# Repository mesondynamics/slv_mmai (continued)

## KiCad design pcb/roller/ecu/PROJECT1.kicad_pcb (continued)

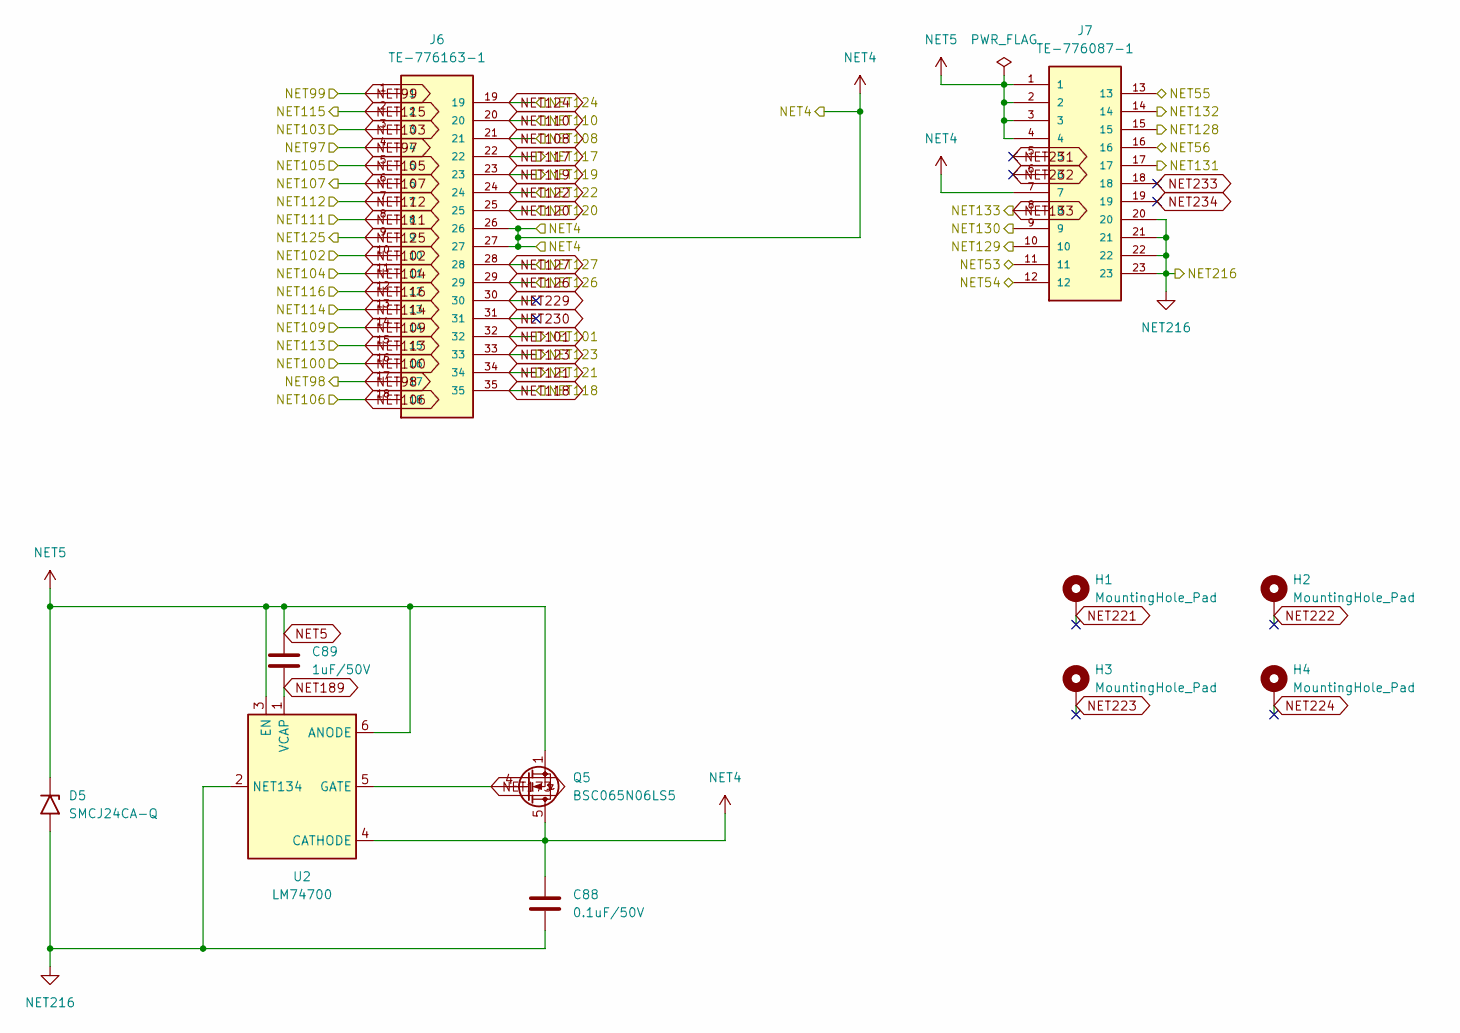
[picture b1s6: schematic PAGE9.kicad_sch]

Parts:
C88: 0.1uF/50V; C_0603_1608Metric
C89: 1uF/50V; C_0603_1608Metric
D5: SMCJ24CA-Q; D_SMC
H1, H2, H3, H4: MountingHole_Pad; MountingHole_3.2mm_M3_ISO7380_Pad
J6: TE-776163-1; TE_776163-1
J7: TE-776087-1; TE_776087-1; PARTREV E11
Q5: BSC065N06LS5; TDSON-8-1
U2: LM74700; SOT-23-6

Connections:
NET4: C88.1, J6.26, J6.27, J7.7, Q5.5 (D), U2.4 (CATHODE); also elsewhere on the board
NET5: C89.1, D5.1 (A1), J7.1, J7.2, J7.3, J7.4, Q5.1 (S), Q5.2 (S), Q5.3 (S), U2.3 (EN), U2.6 (ANODE); also elsewhere on the board
NET53: J7.11; also elsewhere on the board
NET54: J7.12; also elsewhere on the board
NET55: J7.13; also elsewhere on the board
NET56: J7.16; also elsewhere on the board
NET97: J6.4; also elsewhere on the board
NET98: J6.17; also elsewhere on the board
NET99: J6.1; also elsewhere on the board
NET100: J6.16; also elsewhere on the board
NET101: J6.32; also elsewhere on the board
NET102: J6.10; also elsewhere on the board
NET103: J6.3; also elsewhere on the board
NET104: J6.11; also elsewhere on the board
NET105: J6.5; also elsewhere on the board
NET106: J6.18; also elsewhere on the board
NET107: J6.6; also elsewhere on the board
NET108: J6.21; also elsewhere on the board
NET109: J6.14; also elsewhere on the board
NET110: J6.20; also elsewhere on the board
NET111: J6.8; also elsewhere on the board
NET112: J6.7; also elsewhere on the board
NET113: J6.15; also elsewhere on the board
NET114: J6.13; also elsewhere on the board
NET115: J6.2; also elsewhere on the board
NET116: J6.12; also elsewhere on the board
NET117: J6.22; also elsewhere on the board
NET118: J6.35; also elsewhere on the board
NET119: J6.23; also elsewhere on the board
NET120: J6.25; also elsewhere on the board
NET121: J6.34; also elsewhere on the board
NET122: J6.24; also elsewhere on the board
NET123: J6.33; also elsewhere on the board
NET124: J6.19; also elsewhere on the board
NET125: J6.9; also elsewhere on the board
NET126: J6.29; also elsewhere on the board
NET127: J6.28; also elsewhere on the board
NET128: J7.15; also elsewhere on the board
NET129: J7.10; also elsewhere on the board
NET130: J7.9; also elsewhere on the board
NET131: J7.17; also elsewhere on the board
NET132: J7.14; also elsewhere on the board
NET133: J7.8; also elsewhere on the board
NET173: Q5.4 (G), U2.5 (GATE)
NET189: C89.2, U2.1 (VCAP)
NET216: C88.2, D5.2 (A2), J7.20, J7.21, J7.22, J7.23, U2.2 (GND); also elsewhere on the board
NET221: H1.1 (1_1)
NET222: H2.1 (1_1)
NET223: H3.1 (1_1)
NET224: H4.1 (1_1)
NET229: J6.30
NET230: J6.31
NET231: J7.5
NET232: J7.6
NET233: J7.18
NET234: J7.19

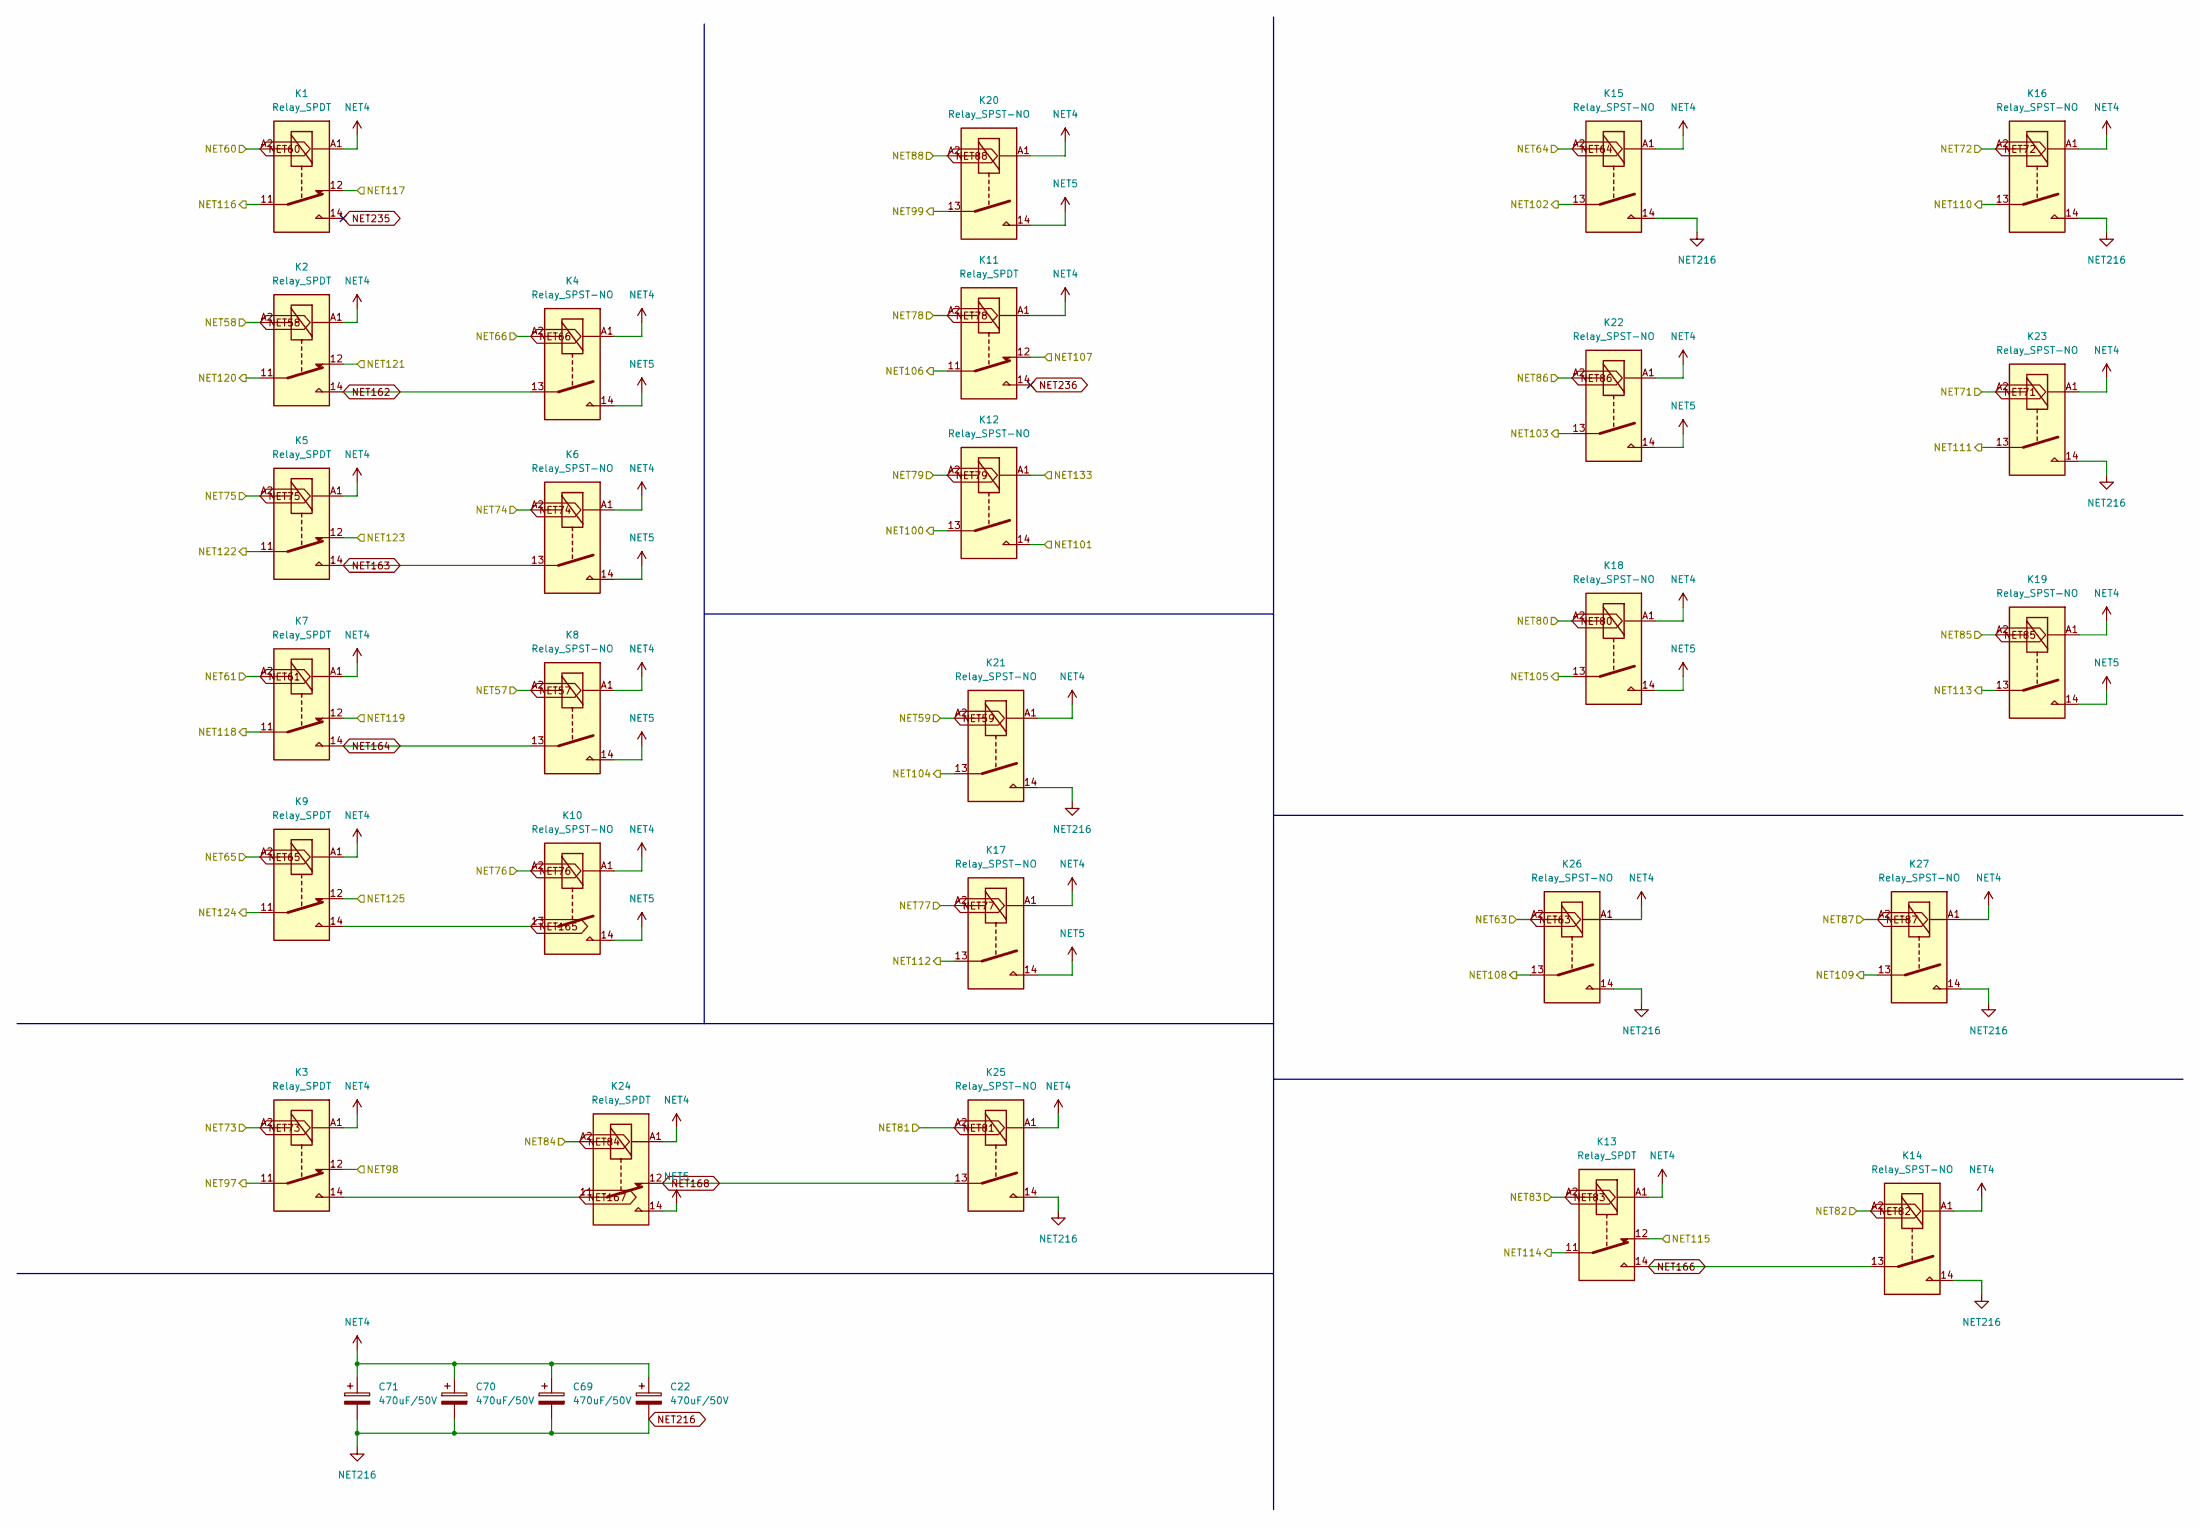
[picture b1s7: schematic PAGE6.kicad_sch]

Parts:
C22, C69, C70, C71: 470uF/50V; CP_Elec_5x5.4
K1, K2, K3, K5, K7, K9, K11, K13, K24: Relay_SPDT; Relay_SPDT_Hongfa_HFV6_1FormC
K4, K6, K8, K10, K12, K14, K15, K16, K17, K18, K19, K20, K21, K22, K23, K25, K26, K27: Relay_SPST-NO; Relay_SPST-NO_Hongfa_HFV6_1FormA

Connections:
NET4: C22.1, C69.1, C70.1, C71.1, K1.A1, K2.A1, K3.A1, K4.A1, K5.A1, K6.A1, K7.A1, K8.A1, K9.A1, K10.A1, K11.A1, K13.A1, K14.A1, K15.A1, K16.A1, K17.A1, K18.A1, K19.A1, K20.A1, K21.A1, K22.A1, K23.A1, K24.A1, K25.A1, K26.A1, K27.A1; also elsewhere on the board
NET5: K4.14, K6.14, K8.14, K10.14, K17.14, K18.14, K19.14, K20.14, K22.14, K24.14; also elsewhere on the board
NET57: K8.A2; also elsewhere on the board
NET58: K2.A2; also elsewhere on the board
NET59: K21.A2; also elsewhere on the board
NET60: K1.A2; also elsewhere on the board
NET61: K7.A2; also elsewhere on the board
NET63: K26.A2; also elsewhere on the board
NET64: K15.A2; also elsewhere on the board
NET65: K9.A2; also elsewhere on the board
NET66: K4.A2; also elsewhere on the board
NET71: K23.A2; also elsewhere on the board
NET72: K16.A2; also elsewhere on the board
NET73: K3.A2; also elsewhere on the board
NET74: K6.A2; also elsewhere on the board
NET75: K5.A2; also elsewhere on the board
NET76: K10.A2; also elsewhere on the board
NET77: K17.A2; also elsewhere on the board
NET78: K11.A2; also elsewhere on the board
NET79: K12.A2; also elsewhere on the board
NET80: K18.A2; also elsewhere on the board
NET81: K25.A2; also elsewhere on the board
NET82: K14.A2; also elsewhere on the board
NET83: K13.A2; also elsewhere on the board
NET84: K24.A2; also elsewhere on the board
NET85: K19.A2; also elsewhere on the board
NET86: K22.A2; also elsewhere on the board
NET87: K27.A2; also elsewhere on the board
NET88: K20.A2; also elsewhere on the board
NET97: K3.11; also elsewhere on the board
NET98: K3.12; also elsewhere on the board
NET99: K20.13; also elsewhere on the board
NET100: K12.13; also elsewhere on the board
NET101: K12.14; also elsewhere on the board
NET102: K15.13; also elsewhere on the board
NET103: K22.13; also elsewhere on the board
NET104: K21.13; also elsewhere on the board
NET105: K18.13; also elsewhere on the board
NET106: K11.11; also elsewhere on the board
NET107: K11.12; also elsewhere on the board
NET108: K26.13; also elsewhere on the board
NET109: K27.13; also elsewhere on the board
NET110: K16.13; also elsewhere on the board
NET111: K23.13; also elsewhere on the board
NET112: K17.13; also elsewhere on the board
NET113: K19.13; also elsewhere on the board
NET114: K13.11; also elsewhere on the board
NET115: K13.12; also elsewhere on the board
NET116: K1.11; also elsewhere on the board
NET117: K1.12; also elsewhere on the board
NET118: K7.11; also elsewhere on the board
NET119: K7.12; also elsewhere on the board
NET120: K2.11; also elsewhere on the board
NET121: K2.12; also elsewhere on the board
NET122: K5.11; also elsewhere on the board
NET123: K5.12; also elsewhere on the board
NET124: K9.11; also elsewhere on the board
NET125: K9.12; also elsewhere on the board
NET133: K12.A1; also elsewhere on the board
NET162: K2.14, K4.13
NET163: K5.14, K6.13
NET164: K7.14, K8.13
NET165: K9.14, K10.13
NET166: K13.14, K14.13
NET167: K3.14, K24.11
NET168: K24.12, K25.13
NET216: C22.2, C69.2, C70.2, C71.2, K14.14, K15.14, K16.14, K21.14, K23.14, K25.14, K26.14, K27.14; also elsewhere on the board
NET235: K1.14
NET236: K11.14

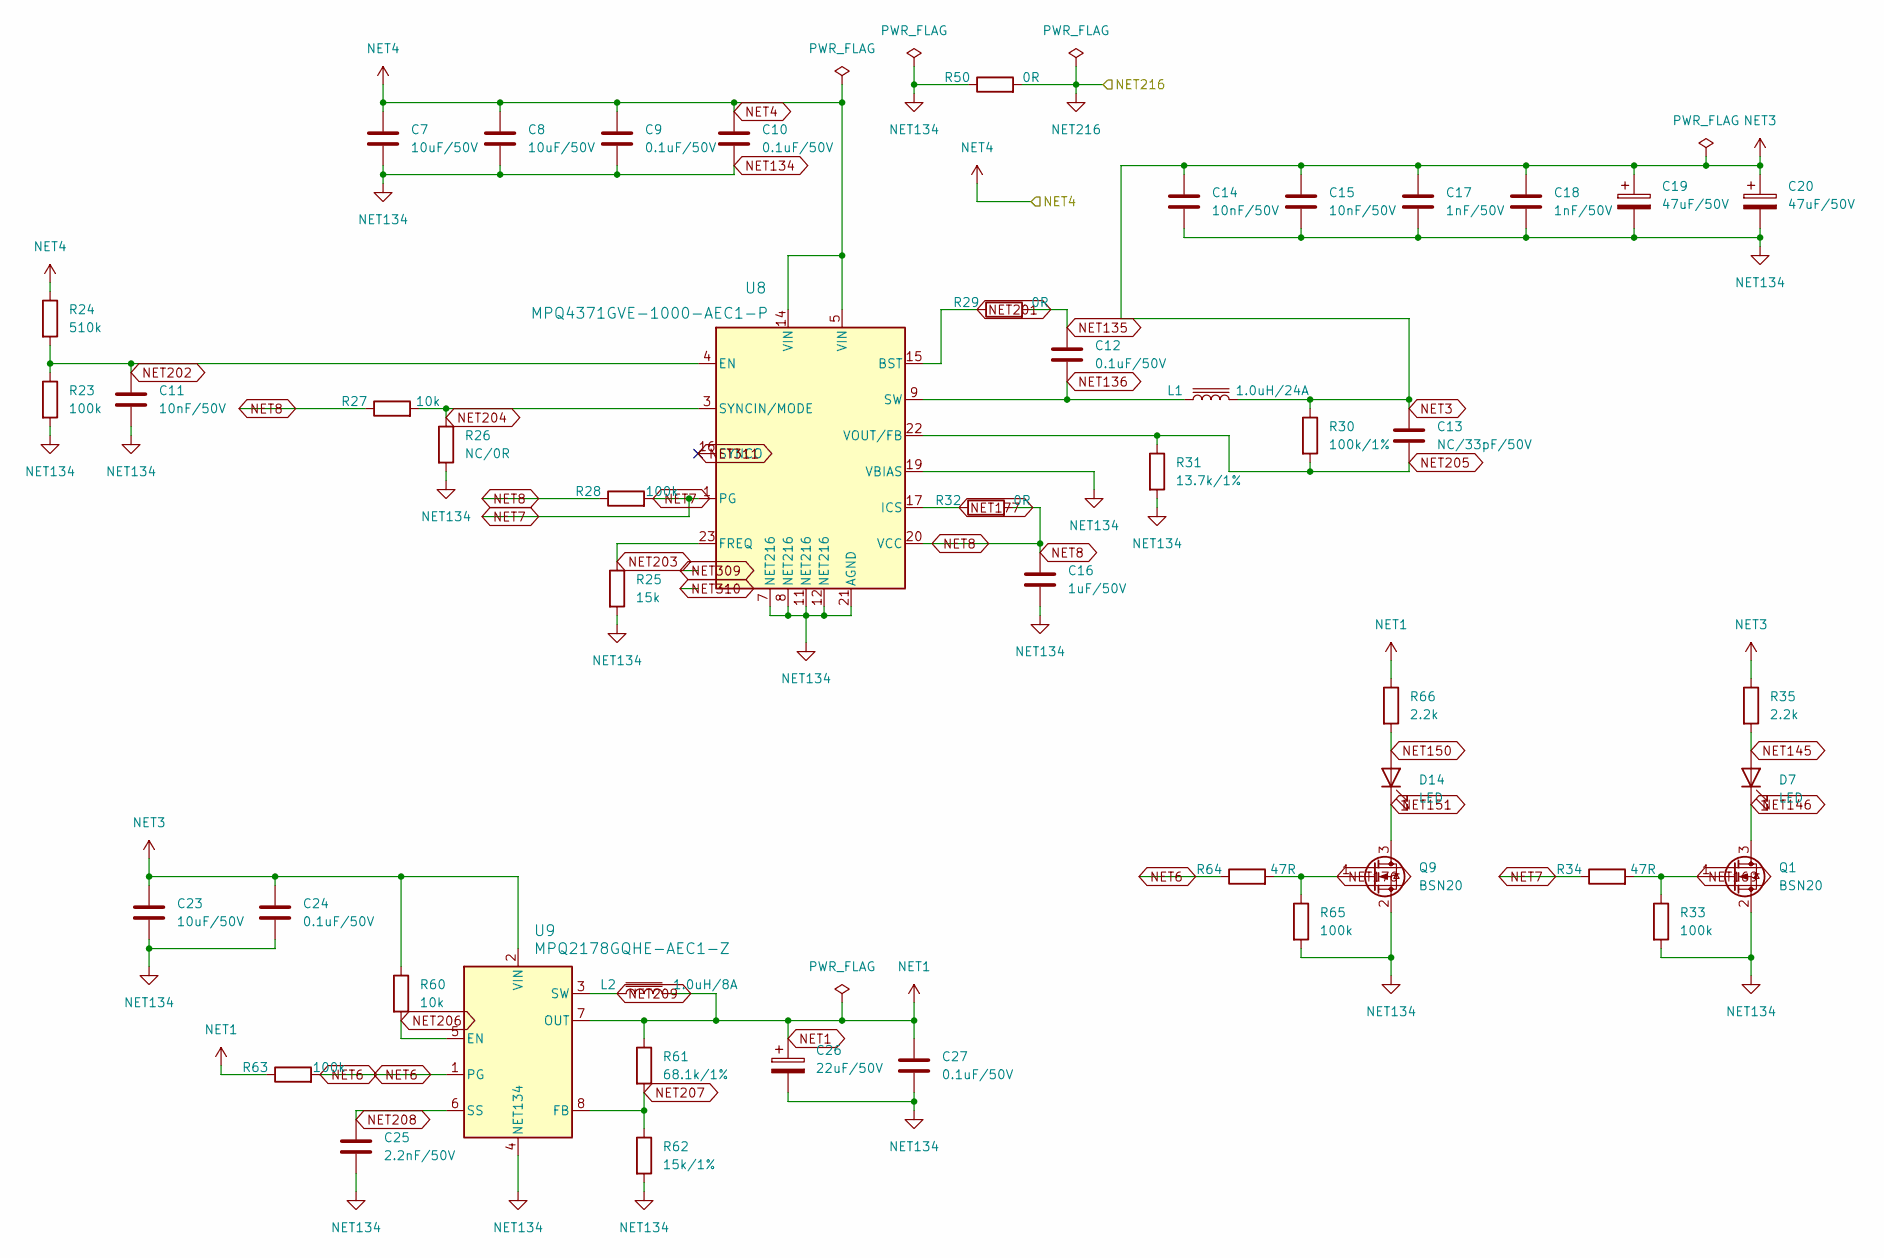
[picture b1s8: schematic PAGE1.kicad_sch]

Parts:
C7, C8, C23: 10uF/50V; C_0603_1608Metric
C9, C10, C12, C24, C27: 0.1uF/50V; C_0603_1608Metric
C11, C14, C15: 10nF/50V; C_0603_1608Metric
C13: NC/33pF/50V; C_0603_1608Metric
C16: 1uF/50V; C_0603_1608Metric
C17, C18: 1nF/50V; C_0603_1608Metric
C19, C20: 47uF/50V; CP_Elec_5x5.4
C25: 2.2nF/50V; C_0603_1608Metric
C26: 22uF/50V; CP_Elec_5x5.4
D7, D14: LED; LED_0603_1608Metric
L1: 1.0uH/24A; L_APV_APH1040
L2: 1.0uH/8A; L_APV_APH0630
Q1, Q9: BSN20; SOT-23
R23, R28, R33, R63, R65: 100k; R_0603_1608Metric
R24: 510k; R_0603_1608Metric
R25: 15k; R_0603_1608Metric
R26: NC/0R; R_0603_1608Metric
R27, R60: 10k; R_0603_1608Metric
R29, R32, R50: 0R; R_0603_1608Metric
R30: 100k/1%; R_0603_1608Metric
R31: 13.7k/1%; R_0603_1608Metric
R34, R64: 47R; R_0603_1608Metric
R35, R66: 2.2k; R_0603_1608Metric
R61: 68.1k/1%; R_0603_1608Metric
R62: 15k/1%; R_0603_1608Metric
U8: MPQ4371GVE-1000-AEC1-P; QFN-234MMX5MM_MPQ4371_MNP
U9: MPQ2178GQHE-AEC1-Z; QFN-8_MPQ2178GQHE

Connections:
NET1: C26.1, C27.1, L2.2, R61.1, R63.1, R66.1, U9.7 (OUT); also elsewhere on the board
NET3: C13.1, C14.1, C15.1, C17.1, C18.1, C19.1, C20.1, C23.1, C24.1, L1.2, R30.1, R35.1, R60.1, U9.2 (VIN); also elsewhere on the board
NET4: C7.1, C8.1, C9.1, C10.1, R24.1, U8.5 (VIN), U8.14 (VIN); also elsewhere on the board
NET6: R63.2, R64.1, U9.1 (PG)
NET7: R28.2, R34.1, U8.1 (PG), U8.2 (PG)
NET8: C16.1, R27.1, R28.1, R32.2, U8.20 (VCC)
NET134: C7.2, C8.2, C9.2, C10.2, C11.2, C14.2, C15.2, C16.2, C17.2, C18.2, C19.2, C20.2, C23.2, C24.2, C25.2, C26.2, C27.2, Q1.2 (S), Q9.2 (S), R23.2, R25.2, R26.2, R31.2, R33.2, R50.1, R62.2, R65.2, U8.7 (PGND), U8.8 (PGND), U8.11 (PGND), U8.12 (PGND), U8.19 (VBIAS), U8.21 (AGND), U9.4 (GND); also elsewhere on the board
NET135: C12.1, R29.2
NET136: C12.2, L1.1, U8.9 (SW), U8.10 (SW)
NET145: D7.2 (A), R35.2
NET146: D7.1 (K), Q1.3 (D)
NET150: D14.2 (A), R66.2
NET151: D14.1 (K), Q9.3 (D)
NET169: Q1.1 (G), R33.1, R34.2
NET176: Q9.1 (G), R64.2, R65.1
NET177: R32.1, U8.17 (ICS), U8.18 (ICS)
NET201: R29.1, U8.15 (BST)
NET202: C11.1, R23.1, R24.2, U8.4 (EN)
NET203: R25.1, U8.23 (FREQ)
NET204: R26.1, R27.2, U8.3 (SYNCIN/MODE)
NET205: C13.2, R30.2, R31.1, U8.22 (VOUT/FB)
NET206: R60.2, U9.5 (EN)
NET207: R61.2, R62.1, U9.8 (FB)
NET208: C25.1, U9.6 (SS)
NET209: L2.1, U9.3 (SW)
NET216: R50.2; also elsewhere on the board
NET309: U8.6 (NC)
NET310: U8.13 (NC)
NET311: U8.16 (SYNCO)

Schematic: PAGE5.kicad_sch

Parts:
C5, C21, C66, C67, C68: 100nF; C_0603_1608Metric
Q6: 2N7002KQ-7; SOT-23
R71: 1.5k; R_0603_1608Metric
R72, R73, R74, R75, R76: 10k; R_0603_1608Metric
R77: 330R; R_0603_1608Metric
R78: 100k; R_0603_1608Metric
U300: SN74AHCT541QPWRQ1; TSSOP-20_4.4x6.5mm_P0.65mm
U301, U302, U303, U304: TPIC6A595DWR; SOIC-24W_7.5x15.4mm_P1.27mm

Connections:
NET3: C5.1, C21.1, C66.1, C67.1, C68.1, R71.1, R72.1, U300.20 (VCC), U301.21 (VCC), U302.21 (VCC), U303.21 (VCC), U304.21 (VCC); also elsewhere on the board
NET33: U300.5 (A3); also elsewhere on the board
NET34: R77.1; also elsewhere on the board
NET35: U300.6 (A4); also elsewhere on the board
NET36: U300.4 (A2); also elsewhere on the board
NET37: U300.2 (A0); also elsewhere on the board
NET38: U300.3 (A1); also elsewhere on the board
NET57: U301.23 (DRAIN0); also elsewhere on the board
NET58: U301.24 (DRAIN1); also elsewhere on the board
NET59: U301.1 (DRAIN2); also elsewhere on the board
NET60: U301.2 (DRAIN3); also elsewhere on the board
NET61: U301.11 (DRAIN4); also elsewhere on the board
NET62: U301.12 (DRAIN5)
NET63: U301.13 (DRAIN6); also elsewhere on the board
NET64: U301.14 (DRAIN7); also elsewhere on the board
NET65: U302.23 (DRAIN0); also elsewhere on the board
NET66: U302.24 (DRAIN1); also elsewhere on the board
NET67: U302.1 (DRAIN2)
NET68: U302.2 (DRAIN3)
NET69: U302.11 (DRAIN4)
NET70: U302.12 (DRAIN5)
NET71: U302.13 (DRAIN6); also elsewhere on the board
NET72: U302.14 (DRAIN7); also elsewhere on the board
NET73: U303.23 (DRAIN0); also elsewhere on the board
NET74: U303.24 (DRAIN1); also elsewhere on the board
NET75: U303.1 (DRAIN2); also elsewhere on the board
NET76: U303.2 (DRAIN3); also elsewhere on the board
NET77: U303.11 (DRAIN4); also elsewhere on the board
NET78: U303.12 (DRAIN5); also elsewhere on the board
NET79: U303.13 (DRAIN6); also elsewhere on the board
NET80: U303.14 (DRAIN7); also elsewhere on the board
NET81: U304.23 (DRAIN0); also elsewhere on the board
NET82: U304.24 (DRAIN1); also elsewhere on the board
NET83: U304.1 (DRAIN2); also elsewhere on the board
NET84: U304.2 (DRAIN3); also elsewhere on the board
NET85: U304.11 (DRAIN4); also elsewhere on the board
NET86: U304.12 (DRAIN5); also elsewhere on the board
NET87: U304.13 (DRAIN6); also elsewhere on the board
NET88: U304.14 (DRAIN7); also elsewhere on the board
NET89: R73.1, U300.15 (Y3), U301.3 (SRCLR_N), U302.3 (SRCLR_N), U303.3 (SRCLR_N), U304.3 (SRCLR_N)
NET90: R72.2, U300.14 (Y4), U301.4 (G_N), U302.4 (G_N), U303.4 (G_N), U304.4 (G_N)
NET91: R74.1, U300.16 (Y2), U301.9 (RCK), U302.9 (RCK), U303.9 (RCK), U304.9 (RCK)
NET92: R76.1, U300.18 (Y0), U301.22 (SERIN)
NET93: R75.1, U300.17 (Y1), U301.10 (SRCK), U302.10 (SRCK), U303.10 (SRCK), U304.10 (SRCK)
NET94: U301.15 (SEROUT), U302.22 (SERIN)
NET95: U302.15 (SEROUT), U303.22 (SERIN)
NET96: U303.15 (SEROUT), U304.22 (SERIN)
NET134: C5.2, C21.2, C66.2, C67.2, C68.2, Q6.2 (S), R73.2, R74.2, R75.2, R76.2, R78.2, U300.7 (A5), U300.8 (A6), U300.9 (A7), U300.10 (GND), U301.16 (LGND), U302.16 (LGND), U303.16 (LGND), U304.16 (LGND); also elsewhere on the board
NET174: Q6.3 (D), R71.2, U300.1 (G1), U300.19 (G2)
NET175: Q6.1 (G), R77.2, R78.1
NET216: U301.5 (PGND1), U301.6 (PGND2), U301.7 (PGND3), U301.8 (PGND4), U301.17 (PGND5), U301.18 (PGND6), U301.19 (PGND7), U301.20 (PGND8), U302.5 (PGND1), U302.6 (PGND2), U302.7 (PGND3), U302.8 (PGND4), U302.17 (PGND5), U302.18 (PGND6), U302.19 (PGND7), U302.20 (PGND8), U303.5 (PGND1), U303.6 (PGND2), U303.7 (PGND3), U303.8 (PGND4), U303.17 (PGND5), U303.18 (PGND6), U303.19 (PGND7), U303.20 (PGND8), U304.5 (PGND1), U304.6 (PGND2), U304.7 (PGND3), U304.8 (PGND4), U304.17 (PGND5), U304.18 (PGND6), U304.19 (PGND7), U304.20 (PGND8); also elsewhere on the board
NET318: U300.13 (Y5)
NET319: U300.12 (Y6)
NET320: U300.11 (Y7)
NET321: U304.15 (SEROUT)

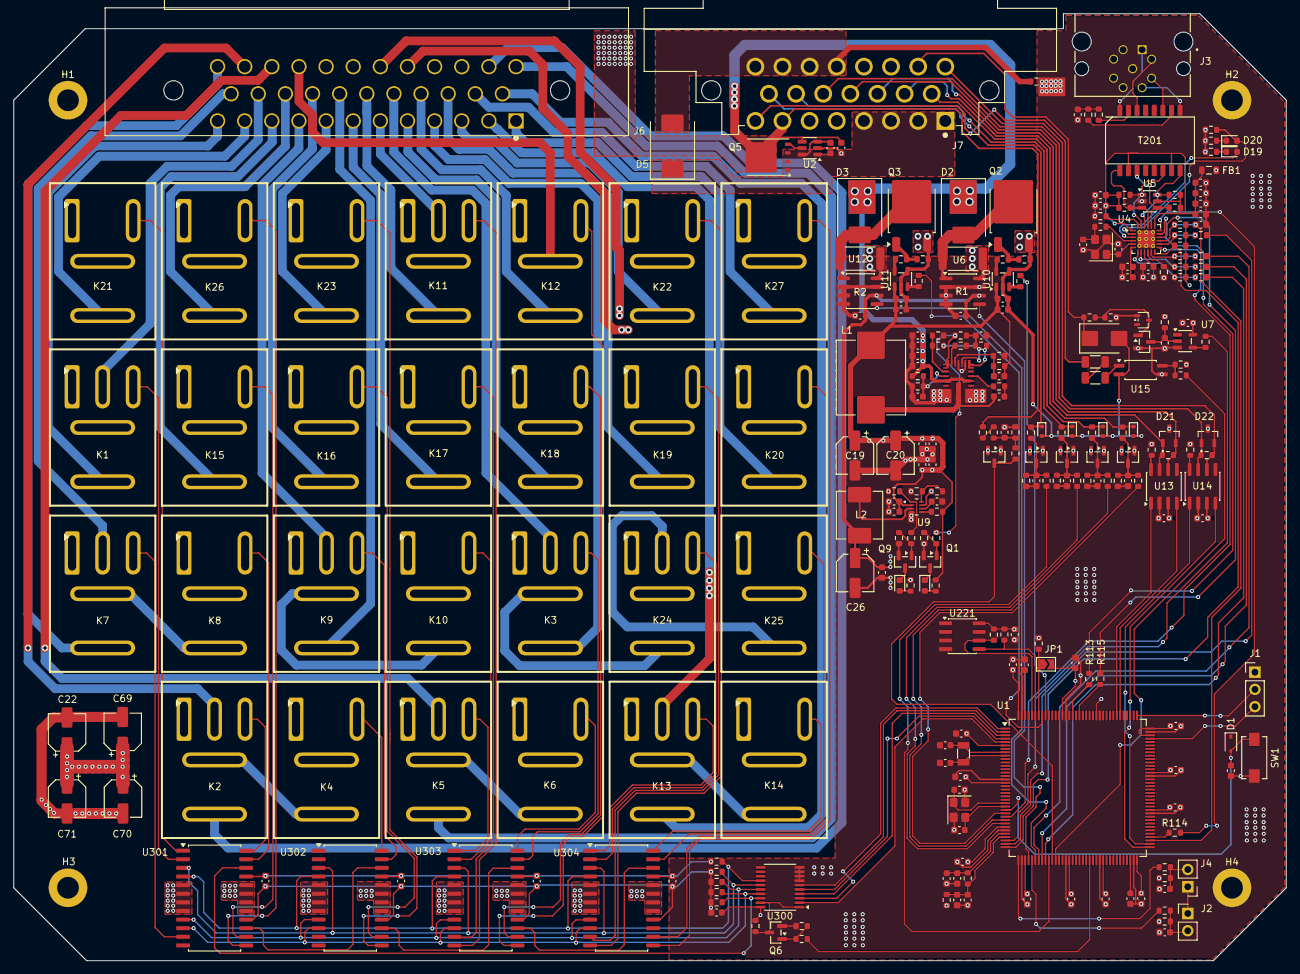
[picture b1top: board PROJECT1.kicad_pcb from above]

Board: 4 copper layers, 187.6 x 139.6 mm, 278 parts (0 on the bottom side), 214 nets.

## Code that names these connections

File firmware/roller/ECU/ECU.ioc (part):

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Mcu.Name=STM32H563ZITx
Mcu.Package=LQFP144
Mcu.UserName=STM32H563ZITx
PA0.GPIOParameters=GPIO_Label,PinAttribute
PA0.GPIO_Label=SPEED_IN
PA0.PinAttribute=CortexM33NS
PA0.Signal=S_TIM2_CH1
PA1.GPIOParameters=GPIO_Speed,GPIO_PuPd,GPIO_Label,GPIO_Mode,PinAttribute
PA1.GPIO_Label=RMII_REF_CLK
PA1.GPIO_Mode=GPIO_MODE_AF_PP
PA1.GPIO_PuPd=GPIO_NOPULL
PA1.GPIO_Speed=GPIO_SPEED_FREQ_LOW
PA1.Mode=RMII
PA1.PinAttribute=CortexM33NS
PA1.Signal=ETH_RMII_REF_CLK
PA13(JTMS/SWDIO).GPIOParameters=GPIO_Label,PinAttribute
PA13(JTMS/SWDIO).GPIO_Label=SWDIO
PA13(JTMS/SWDIO).Mode=Serial_Wire
PA13(JTMS/SWDIO).PinAttribute=CortexM33S
PA13(JTMS/SWDIO).Signal=DEBUG_JTMS-SWDIO
PA14(JTCK/SWCLK).GPIOParameters=GPIO_Label,PinAttribute
PA14(JTCK/SWCLK).GPIO_Label=SWCLK
PA14(JTCK/SWCLK).Mode=Serial_Wire
PA14(JTCK/SWCLK).PinAttribute=CortexM33S
PA14(JTCK/SWCLK).Signal=DEBUG_JTCK-SWCLK
PA2.GPIOParameters=GPIO_Speed,GPIO_PuPd,GPIO_Label,GPIO_Mode,PinAttribute
PA2.GPIO_Label=RMII_MDIO
PA2.GPIO_Mode=GPIO_MODE_AF_PP
PA2.GPIO_PuPd=GPIO_NOPULL
PA2.GPIO_Speed=GPIO_SPEED_FREQ_LOW
PA2.Mode=RMII
PA2.PinAttribute=CortexM33NS
PA2.Signal=ETH_MDIO
PA3.GPIOParameters=GPIO_Label,PinAttribute
PA3.GPIO_Label=TEMP_SENSOR_1_ADC
PA3.PinAttribute=CortexM33S
PA3.Signal=ADCx_INP15
PA4.GPIOParameters=GPIO_Label,PinAttribute
PA4.GPIO_Label=FWD_VALVE_CURR_ADC
PA4.PinAttribute=CortexM33S
PA4.Signal=ADCx_INP18
PA5.GPIOParameters=GPIO_Label,PinAttribute
PA5.GPIO_Label=TEMP_SENSOR_2_ADC
PA5.PinAttribute=CortexM33S
PA5.Signal=ADCx_INP19
PA6.GPIOParameters=GPIO_Label,PinAttribute
PA6.GPIO_Label=REV_VALVE_CURR_ADC
PA6.PinAttribute=CortexM33S
PA6.Signal=ADCx_INP3
PA7.GPIOParameters=GPIO_Speed,GPIO_PuPd,GPIO_Label,GPIO_Mode,PinAttribute
PA7.GPIO_Label=RMII_CRS_DV
PA7.GPIO_Mode=GPIO_MODE_AF_PP
PA7.GPIO_PuPd=GPIO_NOPULL
PA7.GPIO_Speed=GPIO_SPEED_FREQ_LOW
PA7.Mode=RMII
PA7.PinAttribute=CortexM33NS
PA7.Signal=ETH_RMII_CRS_DV
PB0.GPIOParameters=GPIO_Label,PinAttribute
PB0.GPIO_Label=ENGINE_SENSOR_ADC
PB0.PinAttribute=CortexM33S
PB0.Signal=ADCx_INP9
PB1.GPIOParameters=GPIO_Label,PinAttribute
PB1.GPIO_Label=VBAT_12V_ADC
PB1.PinAttribute=CortexM33S
PB1.Signal=ADCx_INP5
PB12.ContextOwner=CortexM33S
PB12.GPIOParameters=GPIO_Label,PinAttribute
PB12.GPIO_Label=CAN2_RX
PB12.Mode=FDCAN_Activate
PB12.PinAttribute=CortexM33S
PB12.Signal=FDCAN2_RX
PB13.ContextOwner=CortexM33S
PB13.GPIOParameters=GPIO_Label,PinAttribute
PB13.GPIO_Label=CAN2_TX
PB13.Mode=FDCAN_Activate
PB13.PinAttribute=CortexM33S
PB13.Signal=FDCAN2_TX
PB14.ContextOwner=CortexM33NS
PB14.GPIOParameters=GPIO_Speed,GPIO_PuPd,GPIO_Label,PinAttribute
PB14.GPIO_Label=RMII_NRST
PB14.GPIO_PuPd=GPIO_NOPULL
PB14.GPIO_Speed=GPIO_SPEED_FREQ_LOW
PB14.PinAttribute=CortexM33NS
PB14.Signal=GPIO_Output
PB15.GPIOParameters=GPIO_Speed,GPIO_PuPd,GPIO_Label,GPIO_Mode,PinAttribute
PB15.GPIO_Label=RMII_TXD1
PB15.GPIO_Mode=GPIO_MODE_AF_PP
PB15.GPIO_PuPd=GPIO_NOPULL
PB15.GPIO_Speed=GPIO_SPEED_FREQ_LOW
PB15.Mode=RMII
PB15.PinAttribute=CortexM33NS
PB15.Signal=ETH_RMII_TXD1
PB2.ContextOwner=CortexM33S
PB2.GPIOParameters=GPIO_PuPd,GPIO_Label,GPIO_ModeDefaultEXTI,PinAttribute
PB2.GPIO_Label=ESTOP_DETECT
PB2.GPIO_ModeDefaultEXTI=GPIO_MODE_IT_RISING_FALLING
PB2.GPIO_PuPd=GPIO_NOPULL
PB2.PinAttribute=CortexM33S
PB2.Signal=GPXTI2
PB6.GPIOParameters=GPIO_Label,PinAttribute
PB6.GPIO_Label=FWD_VALVE_PWM
PB6.PinAttribute=CortexM33S
PB6.Signal=S_TIM4_CH1
PB7.GPIOParameters=GPIO_Label,PinAttribute
PB7.GPIO_Label=REV_VALVE_PWM
PB7.PinAttribute=CortexM33S
PB7.Signal=S_TIM4_CH2
PB8.ContextOwner=CortexM33S
PB8.GPIOParameters=GPIO_Speed,PinState,GPIO_PuPd,GPIO_Label,GPIO_ModeDefaultOutputPP,PinAttribute
PB8.GPIO_Label=SW_I2C_SDA
PB8.GPIO_ModeDefaultOutputPP=GPIO_MODE_OUTPUT_OD
PB8.GPIO_PuPd=GPIO_NOPULL
PB8.GPIO_Speed=GPIO_SPEED_FREQ_LOW
PB8.PinAttribute=CortexM33S
PB8.PinState=GPIO_PIN_SET
PB8.Signal=GPIO_Output
PB9.ContextOwner=CortexM33S
PB9.GPIOParameters=GPIO_Speed,PinState,GPIO_PuPd,GPIO_Label,GPIO_ModeDefaultOutputPP,PinAttribute
PB9.GPIO_Label=SW_I2C_SCL
PB9.GPIO_ModeDefaultOutputPP=GPIO_MODE_OUTPUT_OD
PB9.GPIO_PuPd=GPIO_NOPULL
PB9.GPIO_Speed=GPIO_SPEED_FREQ_LOW
PB9.PinAttribute=CortexM33S
PB9.PinState=GPIO_PIN_SET
PB9.Signal=GPIO_Output
PC0.GPIOParameters=GPIO_Label,PinAttribute
PC0.GPIO_Label=OIL_LEVEL_ADC
PC0.PinAttribute=CortexM33S
PC0.Signal=ADCx_INP10
PC1.GPIOParameters=GPIO_Speed,GPIO_PuPd,GPIO_Label,GPIO_Mode,PinAttribute
PC1.GPIO_Label=RMII_MDC
PC1.GPIO_Mode=GPIO_MODE_AF_PP
PC1.GPIO_PuPd=GPIO_NOPULL
PC1.GPIO_Speed=GPIO_SPEED_FREQ_LOW
PC1.Mode=RMII
PC1.PinAttribute=CortexM33NS
PC1.Signal=ETH_MDC
PC14-OSC32_IN(OSC32_IN).GPIOParameters=PinAttribute
PC14-OSC32_IN(OSC32_IN).Mode=LSE-External-Oscillator
PC14-OSC32_IN(OSC32_IN).PinAttribute=CortexM33S
PC14-OSC32_IN(OSC32_IN).Signal=RCC_OSC32_IN
PC15-OSC32_OUT(OSC32_OUT).GPIOParameters=PinAttribute
PC15-OSC32_OUT(OSC32_OUT).Mode=LSE-External-Oscillator
PC15-OSC32_OUT(OSC32_OUT).PinAttribute=CortexM33S
PC15-OSC32_OUT(OSC32_OUT).Signal=RCC_OSC32_OUT
PC2.GPIOParameters=GPIO_Label,PinAttribute
PC2.GPIO_Label=OIL_TEMP_ADC
PC2.PinAttribute=CortexM33S
PC2.Signal=ADCx_INP12
PC3.GPIOParameters=GPIO_Label,PinAttribute
PC3.GPIO_Label=WATER_LEVEL_ADC
PC3.PinAttribute=CortexM33S
PC3.Signal=ADCx_INP13
PC4.GPIOParameters=GPIO_Speed,GPIO_PuPd,GPIO_Label,GPIO_Mode,PinAttribute
PC4.GPIO_Label=RMII_RXD0
PC4.GPIO_Mode=GPIO_MODE_AF_PP
PC4.GPIO_PuPd=GPIO_NOPULL
PC4.GPIO_Speed=GPIO_SPEED_FREQ_LOW
PC4.Mode=RMII
PC4.PinAttribute=CortexM33NS
PC4.Signal=ETH_RMII_RXD0
PC5.GPIOParameters=GPIO_Speed,GPIO_PuPd,GPIO_Label,GPIO_Mode,PinAttribute
PC5.GPIO_Label=RMII_RXD1
PC5.GPIO_Mode=GPIO_MODE_AF_PP
PC5.GPIO_PuPd=GPIO_NOPULL
PC5.GPIO_Speed=GPIO_SPEED_FREQ_LOW
PC5.Mode=RMII
PC5.PinAttribute=CortexM33NS
PC5.Signal=ETH_RMII_RXD1
PD0.ContextOwner=CortexM33S
PD0.GPIOParameters=GPIO_Label,PinAttribute
PD0.GPIO_Label=CAN1_RX
PD0.Mode=FDCAN_Activate
PD0.PinAttribute=CortexM33S
PD0.Signal=FDCAN1_RX
PD1.ContextOwner=CortexM33S
PD1.GPIOParameters=GPIO_Label,PinAttribute
PD1.GPIO_Label=CAN1_TX
PD1.Mode=FDCAN_Activate
PD1.PinAttribute=CortexM33S
PD1.Signal=FDCAN1_TX
PE2.ContextOwner=CortexM33S
PE2.GPIOParameters=GPIO_Label,PinAttribute
PE2.GPIO_Label=TPIC_SRCK
PE2.Mode=TX_Only_Simplex_Unidirect_Master
PE2.PinAttribute=CortexM33S
PE2.Signal=SPI4_SCK
PE3.ContextOwner=CortexM33S
PE3.GPIOParameters=GPIO_Speed,PinState,GPIO_PuPd,GPIO_Label,PinAttribute
PE3.GPIO_Label=TPIC_OE_N
PE3.GPIO_PuPd=GPIO_NOPULL
PE3.GPIO_Speed=GPIO_SPEED_FREQ_LOW
PE3.PinAttribute=CortexM33S
PE3.PinState=GPIO_PIN_SET
PE3.Signal=GPIO_Output
PE4.ContextOwner=CortexM33S
PE4.GPIOParameters=GPIO_Speed,GPIO_PuPd,GPIO_Label,PinAttribute
PE4.GPIO_Label=TPIC_RCK
PE4.GPIO_PuPd=GPIO_NOPULL
PE4.GPIO_Speed=GPIO_SPEED_FREQ_LOW
PE4.PinAttribute=CortexM33S
PE4.Signal=GPIO_Output
PE5.ContextOwner=CortexM33S
PE5.GPIOParameters=GPIO_Speed,GPIO_PuPd,GPIO_Label,PinAttribute
PE5.GPIO_Label=TPIC_CLR_N
PE5.GPIO_PuPd=GPIO_NOPULL
PE5.GPIO_Speed=GPIO_SPEED_FREQ_LOW
PE5.PinAttribute=CortexM33S
PE5.Signal=GPIO_Output
PE6.ContextOwner=CortexM33S
PE6.GPIOParameters=GPIO_Label,PinAttribute
PE6.GPIO_Label=TPIC_SER
PE6.Mode=TX_Only_Simplex_Unidirect_Master
PE6.PinAttribute=CortexM33S
PE6.Signal=SPI4_MOSI
PE7.ContextOwner=CortexM33S
PE7.GPIOParameters=GPIO_Speed,GPIO_PuPd,GPIO_Label,PinAttribute
PE7.GPIO_Label=TPIC_CTRL_BUF_EN
PE7.GPIO_PuPd=GPIO_NOPULL
PE7.GPIO_Speed=GPIO_SPEED_FREQ_LOW
PE7.PinAttribute=CortexM33S
PE7.Signal=GPIO_Output
PG11.GPIOParameters=GPIO_Speed,GPIO_PuPd,GPIO_Label,GPIO_Mode,PinAttribute
PG11.GPIO_Label=RMII_TX_EN
PG11.GPIO_Mode=GPIO_MODE_AF_PP
PG11.GPIO_PuPd=GPIO_NOPULL
PG11.GPIO_Speed=GPIO_SPEED_FREQ_LOW
PG11.Mode=RMII
PG11.PinAttribute=CortexM33NS
PG11.Signal=ETH_RMII_TX_EN
PG13.GPIOParameters=GPIO_Speed,GPIO_PuPd,GPIO_Label,GPIO_Mode,PinAttribute
PG13.GPIO_Label=RMII_TXD0
PG13.GPIO_Mode=GPIO_MODE_AF_PP
PG13.GPIO_PuPd=GPIO_NOPULL
PG13.GPIO_Speed=GPIO_SPEED_FREQ_LOW
PG13.Mode=RMII
PG13.PinAttribute=CortexM33NS
PG13.Signal=ETH_RMII_TXD0
PH0-OSC_IN(PH0).GPIOParameters=GPIO_Label,PinAttribute
PH0-OSC_IN(PH0).GPIO_Label=RCC_OSC_IN
PH0-OSC_IN(PH0).Mode=HSE-External-Oscillator
PH0-OSC_IN(PH0).PinAttribute=CortexM33S
PH0-OSC_IN(PH0).Signal=RCC_OSC_IN
PH1-OSC_OUT(PH1).Mode=HSE-External-Oscillator
PH1-OSC_OUT(PH1).Signal=RCC_OSC_OUT
RCC.HSE_VALUE=25000000
RCC.SYSCLKFreq_VALUE=250000000
RCC.SYSCLKSource=RCC_SYSCLKSOURCE_PLLCLK
board=custom

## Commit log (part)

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2024-12-26 Created repo and point submodule slv_ardupilot to slv branch.
2025-01-23 Update submodule slv_ardupilot to latest commit
2025-04-23 Refactor code structure and remove redundant sections
2025-04-23 Add STM32 CubeMX Cmake project
2025-04-23 Add ATK-DMF407 V1.2 PDF documentation
2025-04-23 Enhance GPS data handling: add orientation fields, update covariance structure, and refactor GPS data processing in main
2025-04-23 Fix odometry calculations: negate left encoder counts in initialization, update, reset, and data retrieval functions
2025-04-23 Enhance GPS data processing: add reception timestamp parameter to gps_process_data function and update main to utilize it
2025-04-24 STM32CubeMX configuration Ethernet and LwIP
2025-04-24 Add YT8512C driver files and integrate with Ethernet interface
2025-04-24 Add TCP server implementation: create tcp_server.c and tcp_server.h, integrate into main
2025-04-24 Add Protocol
2025-04-28 Implement communication protocol and integrate encoder data publishing
    - Added protocol.c to handle communication protocol implementation.
    - Introduced functions for packing and unpacking various data types including encoder parameters, GPS parameters, and EKF data.
    - Updated main.c to publish encoder data over TCP, including encoder parameters and counts.
    - Implemented CRC-8 checksum calculation for data integrity.
    - Enhanced data handling by defining expected packet sizes and managing data buffers for different frame types.
2025-04-28 Refactor encoder data handling: unify frame type and update data structure for multiple encoder counts
2025-04-28 Refactor encoder data packing: remove frame type parameter and set it internally
2025-04-28 Refactor GPS data handling: update data structures and functions for improved GPS data processing and communication protocol integration
2025-04-28 Refactor GPS module: add quaternion calculations and update data handling for local transformation
2025-04-28 Refactor protocol: update frame counts for GPS raw and position data, rename packing function for clarity
2025-04-28 Refactor GPS and protocol handling: update gps_process_data to return status, modify GPS data processing flow, and adjust IP address configuration in lwip.c
2025-04-28 Fix TIM2 initialization: correct timer period value from 4294967295 to 65535
2025-04-29 Refactor encoder data handling: streamline timestamp assignment and optimize send buffer allocation for TCP transmission
2025-04-29 Refactor odometry data structure and update related functions
    - Changed odometry data structure from `odometry_t` to `odometry_data_t` for clarity and consistency.
    - Updated odometry initialization, update, and reset functions to reflect the new data structure.
    - Modified odometry calculations to use new parameters such as `encoder_pulse_per_rev` and `gear_ratio`.
    - Updated protocol functions to pack and parse odometry data correctly.
    - Adjusted main application logic to handle the new odometry data structure and send odometry data over TCP.
    - Refined parameter handling to replace `encoder_resolution` with `encoder_pulse_per_rev` and `time_scaling` with `gear_ratio`.
2025-04-29 Refactor odometry module: replace odometry data structure with separate wheel odometry and encoder data handling functions
2025-04-29 Update heading calculation in gps_parse_headinga and remove commented debug prints in main
2025-04-29 Refactor protocol documentation: update section headings, improve clarity, and correct data structure descriptions
2025-05-10 Refactor GPS constants: rename WGS84 constants for clarity and consistency in gps.h and gps.c
2025-05-10 Implement sensor fusion for odometry and GPS using EKF: add fusion.c and fusion.h, integrate EKF initialization and updates in main.c
2025-05-14 Refactor EKF process noise parameters: adjust uncertainties for position, yaw, velocity, and angular velocity in fusion.c; update odometry handling in main.c to improve data management and logging.
2025-06-09 Add GPS parameters and update initialization values: include offsets for GPS to front axle and heading in parameters.h and parameters.c; modify wheel radius and wheelbase values for improved accuracy.
2025-06-11 Add ADC functionality and steering angle data handling: create adc.c and adc.h for ADC configuration; initialize ADC in main.c; read and process steering angle data; update protocol for steering angl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
2025-06-18 Add filtering to steering angle data
2025-06-24 Refactor GPS handling and add support for dual GPS modules
    - Split GPS reception into front and rear modules with separate buffers and processing logic.
    - Update UART initialization to include USART6 for rear GPS.
    - Modify main loop to handle new GPS data from both front and rear modules.
    - Adjust protocol handling to differentiate between front and rear GPS raw data.
    - Remove unused encoder initialization and related code for TIM2 and TIM3.
    - Clean up debug print statements and unnecessary TCP data publishing logic.
2025-06-24 feat: Update ADC configuration and add USART6 support
    - Configured ADC1 Channel 1 to use ADC_CHANNEL_3 with a sampling time of 15 cycles.
    - Added USART6 to the project and updated its parameters for asynchronous mode.
    - Adjusted the pin assignments for ADC1 and USART6, ensuring proper signal mapping.
    - Modified the project settings to reflect the changes in the function list and firmware version.
    - Removed unused timer configurations related to TIM2 and TIM3.
2025-06-24 feat: Add CAN communication support with message filtering and processing
2025-06-24 feat: Add radar object handling and parsing functions for CAN messages
2025-06-24 feat: Implement CAN message circular buffer and processing functions
2025-06-25 Refactor code structure for improved readability and maintainability
2025-06-25 feat: Add MMW data packing and structure definitions for radar processing
2025-06-25 feat: Implement radar timeout handling and send empty data when no updates are received
2025-07-24 feat: Add USART1 and USART2 initialization and interrupt handling
2025-07-25 feat: Update baud rate for UART5 and USART2 to 921600
2025-07-25 feat: Add IMU data acquisition and processing module with UART integration
2025-07-28 feat: Add DMA configuration and interrupt handling for UART5 and USART2
2025-07-28 feat: Remove ADC module and related configurations from the project
2025-07-28 feat: Remove unused IMU and USART data processing code from main.c
2025-07-28 feat: Add UART queue management implementation and integrate with IMU data processing
2025-07-28 feat: Add frequency statistics module with initialization and calculation functions
2025-07-28 feat: Implement UART reception callback for IMU data processing and update usart.c and main.c
2025-07-28 feat: Refactor IMU and AHRS data structures and update protocol handling for front and rear IMU data
2025-07-28 feat: Refactor GPS initialization to remove UART parameter and streamline data processing
2025-09-11 feat: Add IMU debugging variables and update UART reception handling for improved data processing
2025-09-15 Refactor IMU handling and UART configuration
    - Removed IMU2 related code and structures to streamline IMU processing.
    - Updated UART configuration to use USART3 instead of UART5 for IMU1.
    - Adjusted DMA settings and interrupt handlers to accommodate the new USART3 configuration.
    - Enhanced debug output for IMU1 data processing, including detailed packet structure logging.
    - Modified the STM32CubeMX project file to reflect changes in UART and DMA settings.
    - Updated IP address settings in the project configuration for network connectivity.
2025-09-15 feat: Add support for dual IMU data processing with UART2 integration and DMA configuration
2025-09-15 refactor: Remove conditional compilation for IMU debugging variables and update IMU data frame type in main function
2025-09-16 Update IMU and GPS handling with enhanced queue management and DMA integration
    - Changed copyright notice in imu.c and uart_queue.c to reflect new company name.
    - Updated debug settings in main.c to disable debug prints by default.
    - Refactored GPS data handling to use dedicated queues for front and rear GPS data.
    - Implemented generic queue functions for IMU and GPS data processing.
    - Added DMA configuration for UART4 and USART6 to improve data reception.
    - Removed legacy GPS data reception handling in HAL_UART_RxCpltCallback.
2025-09-17 feat: Add LED GPIO configurations and update main loop for LED toggling
2025-09-17 feat: Enhance IMU and GPS handling with increased queue sizes and DMA priority adjustments
2025-09-17 feat: Update IMU handling and GPIO configurations for improved data processing and LED control
2025-09-18 refactor: Remove unused DMA configurations and update GPS data handling in main loop
2025-09-25 fix: Correct UART instance assignments for GPS data reception
2025-09-25 feat: Enhance GPS data parsing with additional field validation
2025-09-25 fix: Add missing file associations for GPS and fusion headers in VSCode settings
2025-09-25 feat: Add GPIO switch configurations and EXTI interrupt handlers for improved input handling
2025-09-25 feat: Add joystick data handling with packing function and frame type definition
2025-09-25 fix: Update JOY_DATA_FRAME_COUNT comment for clarity and change joystick state array type to uint8_t
2025-09-25 feat: Add switch counters and GPIO EXTI callback for improved switch handling
2025-09-25 feat: Implement joy data transmission at 10Hz with switch count packing and sending
2025-09-29 fix: Update radar object distance resolution and offsets for accuracy in parsing
2026-03-02 Add Control Cabinet Wiring Diagram
2026-03-16 feat: Add GPS initialization commands and RTCM parsing for TCP server
2026-03-16 feat: Add LED control commands and protocol packet handling in TCP server
2026-06-30 Initialize STM32 CubeMX Project
